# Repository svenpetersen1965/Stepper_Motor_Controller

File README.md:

# Stepper Motor Controller
The purpose of this project is top provide an Arduino (Pro Micro) based stepper motor controller with two output channels, rotary encoder, LCD display and an RS-232 interface (beside the serial via USB interface of the Pro Micro) with a 3D printed case and a software framework (Arduino Sketch) suitable for many purposes.

The 3D printed case provides different versions of the top and bottom shells. 

In case you are not experienced with cable making, you might want to read the <a href="http://tech.guitarsite.de/cable_making.html">essay about this topic on my website</a>.

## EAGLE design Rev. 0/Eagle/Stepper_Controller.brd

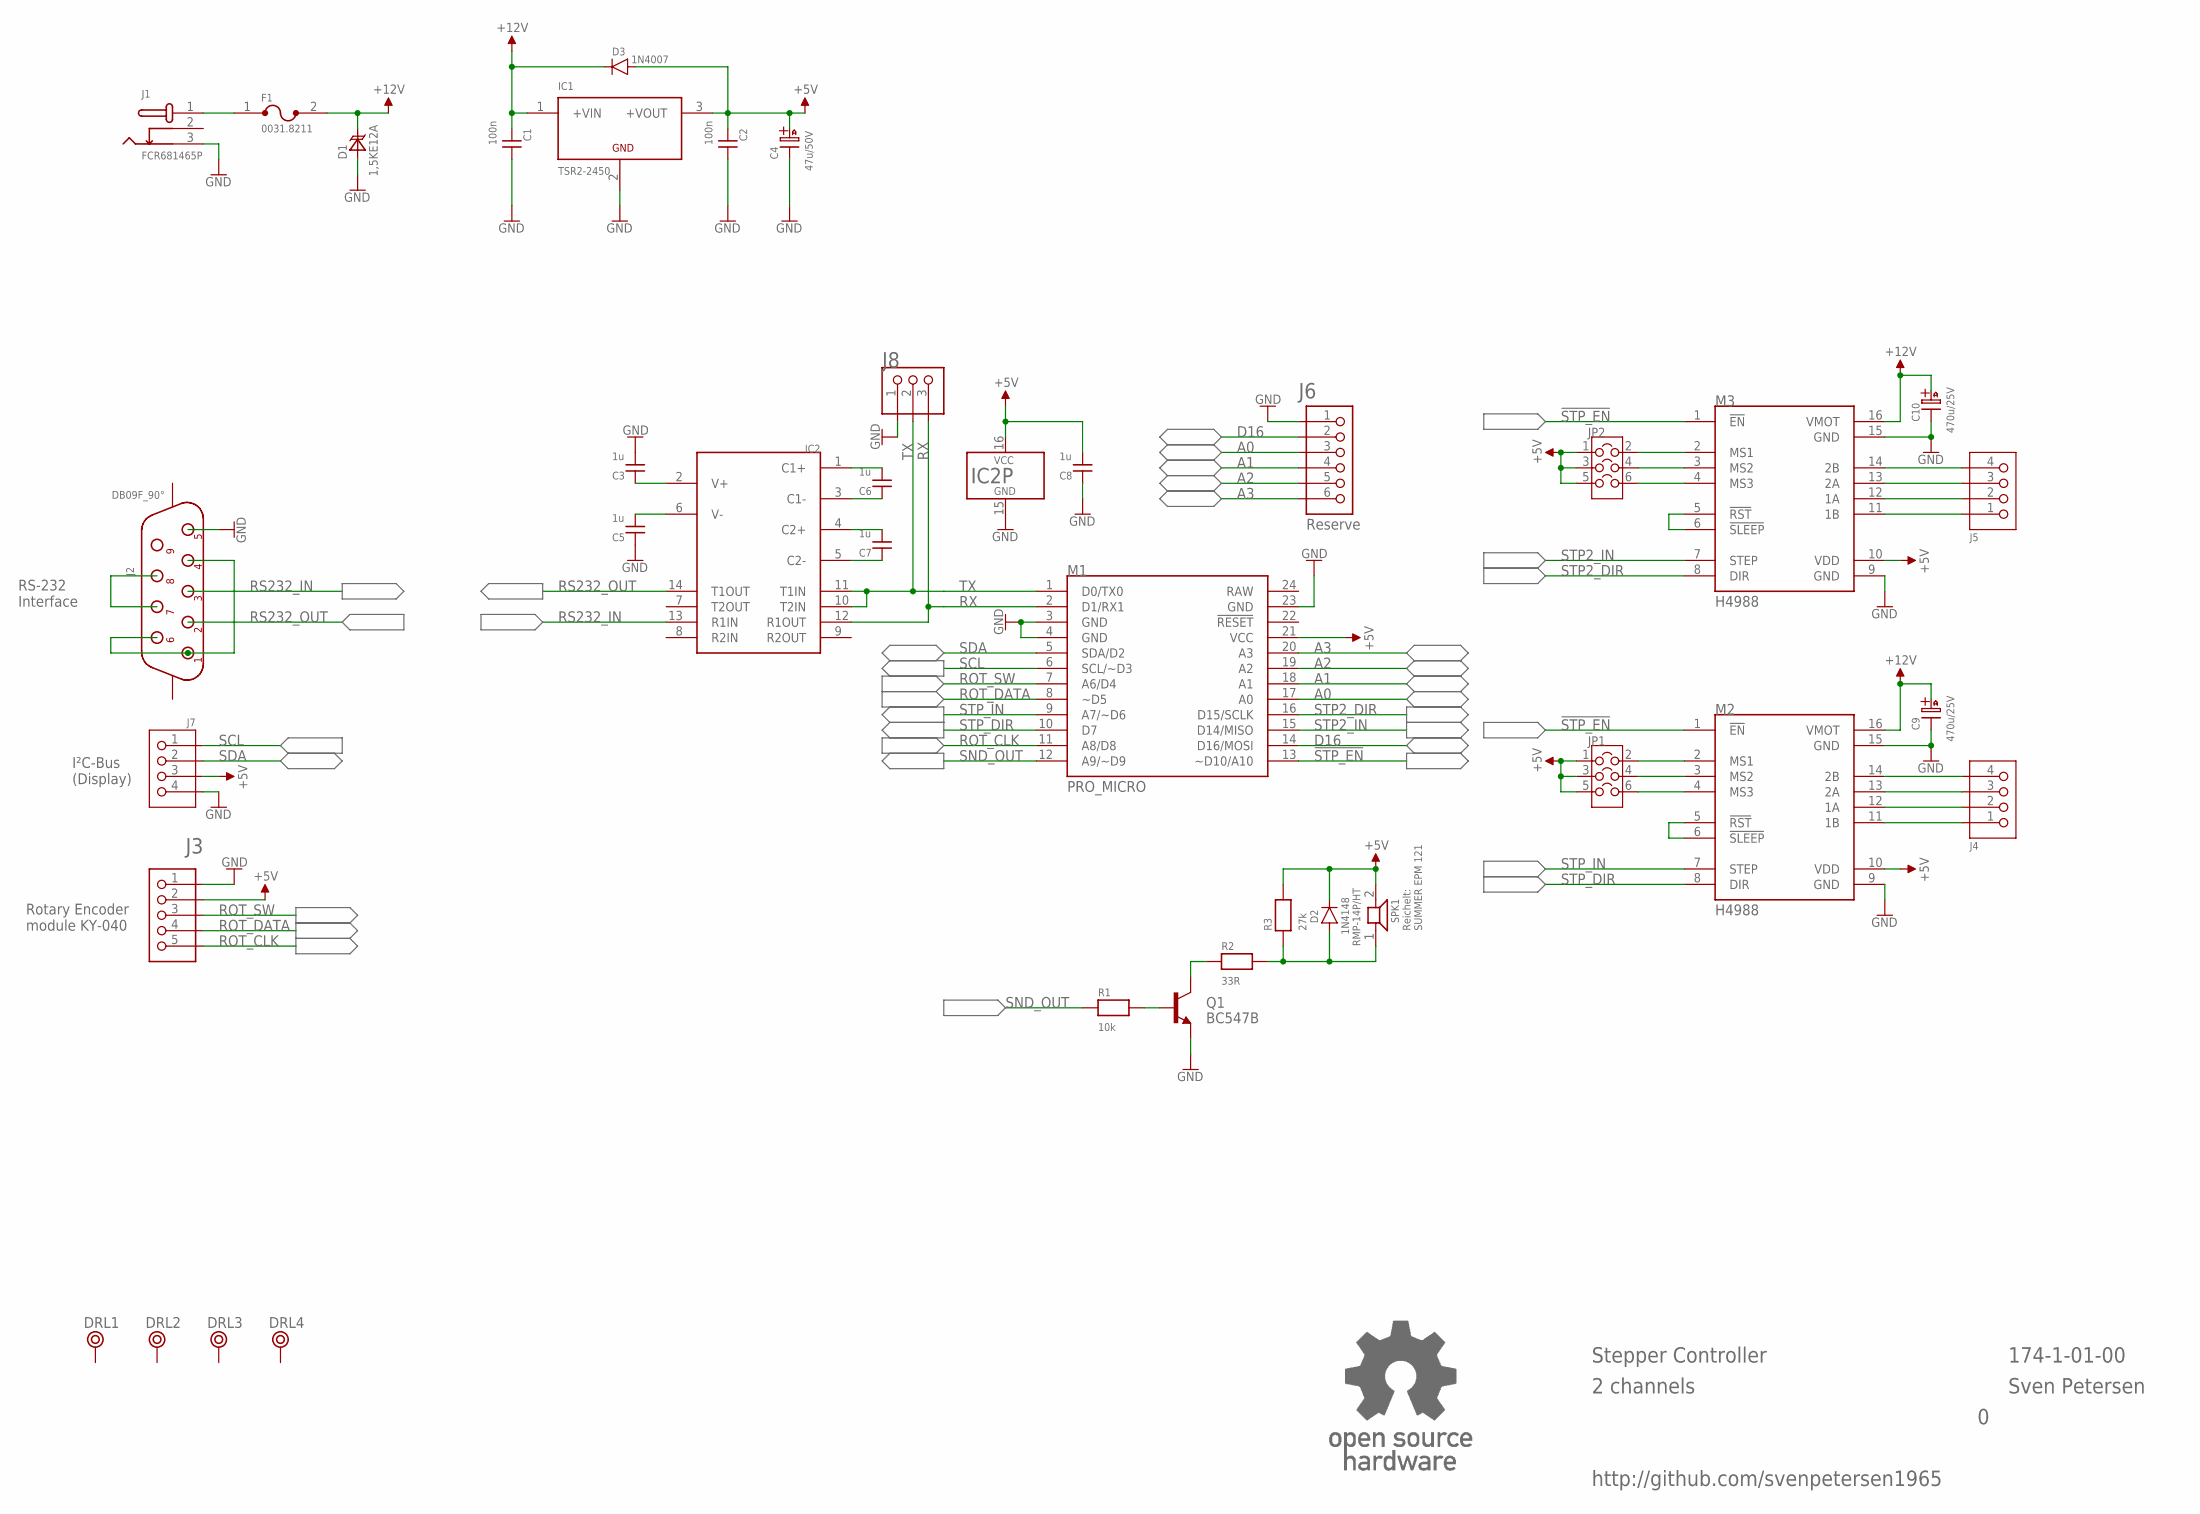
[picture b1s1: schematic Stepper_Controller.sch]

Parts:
C1, C2: 100n; C-2,5
C3, C5, C6, C7, C8: 1u; C-5
C4: 47u/50V; C07/2,5
C9, C10: 470u/25V; C08/3,5
D1: 1,5KE12A; DO-201
D2: 1N4148; DO-35
D3: 1N4007; DO-41
DRL1, DRL2, DRL3, DRL4: BOHR3,5
F1: 0031.8211
IC1: TSR2-2450; TSR2
IC2: MAX-232; DIL-16
J1: FCR681465P
J2: DB09F_90°; DS09F-H
J3: 6410-5P
J4, J5, J7: 6410-4P
J6: PINHD-1X6; 1X06
J8: PINHD-1X3; 1X03
JP1, JP2: COMBI-3X2P; COMBI-3X2
M1: PRO_MICRO
M2, M3: H4988
Q1: BC547B; TO92
R1: 10k; R-10
R2: 33R; R-10
R3: 27k; R-10
SPK1: RMP-14P/HT
U$2: OPEN_SOURCE_HW; OPENHW

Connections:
!STP_EN: M1.13 (~D10/A10), M2.1 (!EN), M3.1 (!EN)
+5V: C2.1, C4.A (+), C8.2, D2.K, D3.A, IC1.3 (+VOUT), IC2.16 (VCC), J3.2, J7.3, JP1.1, JP1.3, JP1.5, JP2.1, JP2.3, JP2.5, M1.21 (VCC), M2.10 (VDD), M3.10 (VDD), R3.2, SPK1.2
+12V: C1.1, C9.+, C10.+, D1.K, D3.K, F1.2, IC1.1 (+VIN), M2.16 (VMOT), M3.16 (VMOT)
A0: J6.3, M1.17 (A0)
A1: J6.4, M1.18 (A1)
A2: J6.5, M1.19 (A2)
A3: J6.6, M1.20 (A3)
D16: J6.2, M1.14 (D16/MOSI)
GND: C1.2, C2.2, C3.2, C4.K (-), C5.1, C8.1, C9.-, C10.-, D1.A, IC1.2 (GND), IC2.15 (GND), J1.3, J2.5, J3.1, J6.1, J7.4, J8.1, M1.3 (GND), M1.4 (GND), M1.23 (GND), M2.9 (GND), M2.15 (GND), M3.9 (GND), M3.15 (GND), Q1.1 (E)
unnamed: F1.1, J1.1
unnamed: Q1.3 (C), R2.1
unnamed: Q1.2 (B), R1.2
unnamed: J2.1, J2.4, J2.6
unnamed: J2.7, J2.8
unnamed: C7.2, IC2.4 (C2+)
unnamed: C7.1, IC2.5 (C2-)
unnamed: C6.1, IC2.3 (C1-)
unnamed: C6.2, IC2.1 (C1+)
unnamed: D2.A, R2.2, R3.1, SPK1.1
unnamed: C3.1, IC2.2 (V+)
unnamed: C5.2, IC2.6 (V-)
unnamed: M2.5 (!RST), M2.6 (!SLEEP)
unnamed: M3.5 (!RST), M3.6 (!SLEEP)
unnamed: JP2.2, M3.2 (MS1)
unnamed: JP2.4, M3.3 (MS2)
unnamed: JP2.6, M3.4 (MS3)
unnamed: JP1.2, M2.2 (MS1)
unnamed: JP1.4, M2.3 (MS2)
unnamed: JP1.6, M2.4 (MS3)
unnamed: J4.1, M2.11 (1B)
unnamed: J4.2, M2.12 (1A)
unnamed: J4.3, M2.13 (2A)
unnamed: J4.4, M2.14 (2B)
unnamed: J5.1, M3.11 (1B)
unnamed: J5.2, M3.12 (1A)
unnamed: J5.3, M3.13 (2A)
unnamed: J5.4, M3.14 (2B)
RAW: M1.24 (RAW)
ROT_CLK: J3.5, M1.11 (A8/D8)
ROT_DATA: J3.4, M1.8 (~D5)
ROT_SW: J3.3, M1.7 (A6/D4)
RS232_IN: IC2.13 (R1IN), J2.3
RS232_OUT: IC2.14 (T1OUT), J2.2
RX: IC2.12 (R1OUT), J8.3, M1.2 (D1/RX1)
SCL: J7.1, M1.6 (SCL/~D3)
SDA: J7.2, M1.5 (SDA/D2)
SND_OUT: M1.12 (A9/~D9), R1.1
STP2_DIR: M1.16 (D15/SCLK), M3.8 (DIR)
STP2_IN: M1.15 (D14/MISO), M3.7 (STEP)
STP_DIR: M1.10 (D7), M2.8 (DIR)
STP_IN: M1.9 (A7/~D6), M2.7 (STEP)
TX: IC2.10 (T2IN), IC2.11 (T1IN), J8.2, M1.1 (D0/TX0)

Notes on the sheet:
I²C-Bus (Display)
Reichelt: SUMMER EPM 121
RS-232 Interface
Rotary Encoder module KY-040
Reserve
Stepper Controller
2 channels
174-1-01-00
Sven Petersen
http://github.com/svenpetersen1965

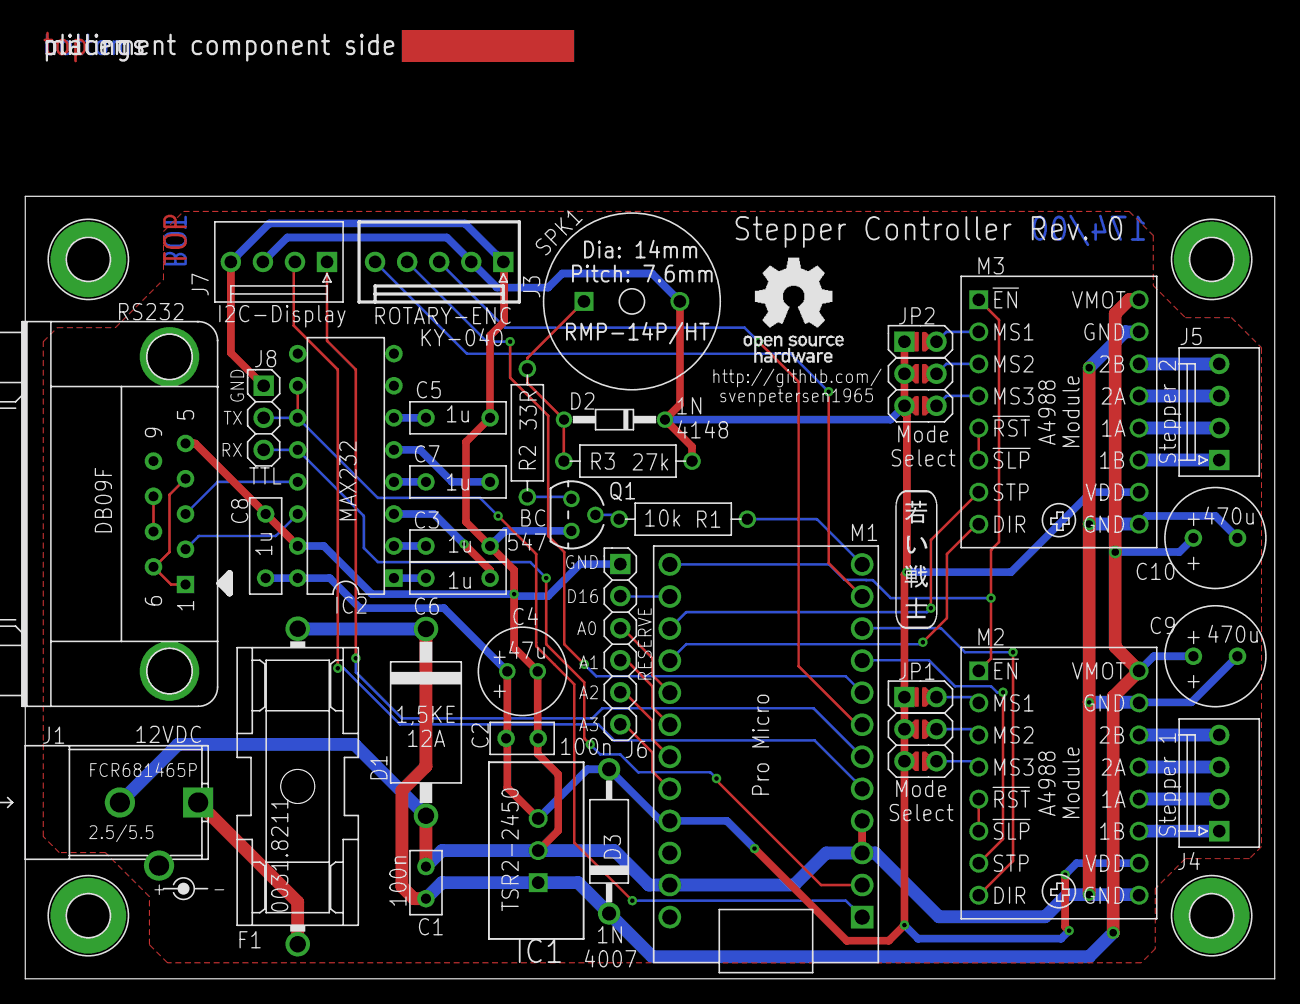
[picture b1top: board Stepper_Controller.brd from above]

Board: 2 copper layers, 99.0 x 75.6 mm, 42 parts (0 on the bottom side), 51 nets.

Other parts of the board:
U$59: PCB-TITLE/
U$71: SVEN_TAG
U$77: 2LAYER

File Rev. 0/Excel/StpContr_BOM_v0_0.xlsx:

Stepper Motor Controller Rev. 0
Bill of Material Rev. 0.0
Pos. | Qty | Value | Footprint | Ref.-No. | Comment
1 | 1 | 174-2-01-00 | 2 Layer | PCB Rev. 0 | 2 layer, Cu 35µ, HASL, 99.0mm x 62.0mm, 1.6mm FR4
2 | 2 | KF2510 (vertical, 4pin) | 6410-4P | J4, J5 | or Molex 22-27-2041 (vertical, Reichelt MOLEX 22272041 or tme.eu:MX-6410-04A) o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
3 | 1 | KF2510 (vertical, 4pin) | 6410-4P | J7 | or Molex 22-27-2041 (always vertical, Reichelt MOLEX 22272041 or tme.eu:MX-6410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
4 | 3 | KF2510 crimp housing, 4 pins |  | (J4), (J5), (J6) | or Molex 22013047 (Reichelt: MOLEX 22013047, tme.eu: MX-22-01-3047)
5 | 12 | KF2510 crimp terminals |  | (J4), (J5), (J6) | or Molex 08500114 (Reichelt: MOLEX 8500114) or Molex 08-70-0049 (tme.eu: MX-08-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
6 | 1 | KF2510 (vertical, 5pin) | 6410-5P | J3 | or Molex 22-27-2051
7 | 1 | KF2510 crimp housing, 4 pins |  | (J3) | or Molex 22013057
8 | 5 | KF2510 crimp terminals |  | (J3) | or Molex 08500114 (Reichelt: MOLEX 8500114) or Molex 08-70-0049 (tme.eu: MX-08-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
9 | 1 | MAX232CPE | DIL-16 | IC2 | Maxim or Renesas HIN232CPZ (Reichelt: MAX 232 DIP, tme.eu: HIN232CPZ)
10 | 1 | pin header, 3 pin, 2.54mm pitch | 1X03 | J8 | DNP
11 | 1 | pin header, 6 pin, 2.54mm pitch | 1X06 | J6 | DNP
12 | 1 | 0031.8211 | 318211 | F1 | Schurter fuse holder (Reichelt: PL OGN-25, tme.eu: 0031.8211)
13 | 1 | 5x20mm, 3.15AT |  | (F1) | This fuse depends on the power supply and the application
14 | 1 | 1,5KE12A | DO-201 | D1 | TVS-Diode, unidirektional, (Reichelt: 1,5KE 12A, tme.eu: 1.5KE12A-LF)
15 | 2 | 100n | C-2,5 | C1, C2 | ceramic capacitor, 2.5mm pitch
16 | 1 | 10k | R-10 | R1 | metal film resistor, 0.5W (or more), 5% or better
17 | 1 | 1N4007 | DO-41 | D3 | diode
18 | 1 | 1N4148 | DO-35 | D2 | diode
19 | 5 | 1u | C-5 | C3, C5, C6, C7, C8 | ceramic capacitor, 5mm pitch (e.g. Reichelt Z5U-5 1,0µ)
20 | 1 | 27k | R-10 | R3 | metal film resistor, 0.5W (or more), 5% or better
21 | 1 | 33R | R-10 | R2 | metal film resistor, 0.5W (or more), 5% or better
22 | 2 | 470u/25V | C08/3,5 | C9, C10 | e-cap, Æ8mm, pitch 3.5mm, 105°C, e.g. Reichelt RAD FC 470/25
23 | 1 | 47u/50V | C07/2,5 | C4 | e-cap, Æ7mm, pitch 2.5mm, 105°C, e.g. Reichelt RAD FC 47/50
24 | 1 | BC547B | TO92 | Q1 | universal NPN Transistor
25 | 2 | COMBI-3X2P | COMBI-3X2 | JP1, JP2 | see document 174-6-01-**. Reichelt MPE 087-2-006
26 | 1 | DB09F_90° | DS09F-H | J2 | D-Sub, 9pin, female, 90°, (Reichelt
27 | 1 | FCR681465P | FCR681465P | J1 | Cliff barrel connector (2.5mm/5.5mm), Reichelt: CLIFF FCR681465P, tme.eu: FCR68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
28 | 2 | A4988 | H4988 | M2, M3 | A4988 stepper driver module (AliExpress or Ebay etc.)
29 | 4 | 1x8 socket strip, 2.54mm |  | (M2), (M3) | e.g. MPE 115-1-008 (Reichelt: MPE 115-1-008, tme.eu: ZL307-1X8)
30 | 1 | PRO_MICRO | PRO_MICRO | M1 | 16MHz, 5V, Micro Controller module (Arduino compatible) from AliExpress, Ebay e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
31 | 2 | 1x12 socket strip, 2.54mm |  | (M1) | e.g. MPE 115-1-012 (Reichelt: MPE 115-1-012, tme.eu: ZL262-12SG)
32 | 1 | RMP-14P/HT | RMP-14P/HT | SPK1 | piezzo buzzer, Æ14mm, pitch 7.6mm, EKULIT (Reichelt SUMMER EPM 121): alternativ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
33 | 1 | 7805 or TSR2-2450 | TSR2 | IC1 | standard linear regulator or Traco DC/DC converter for higher supply voltages
34 | 1 | LCD Display I²C, 16x2 |  | (J7) | "standard" product from Ebay or AliExpress.
35 | 1 | dupont crimp housing, 4 pins |  |  | For the I²C Display cable
36 | 4 | Dupont crimp terminals |  |  | For the I²C Display cable
37 | 14cm | cable, AWG24, black |  |  | For the I²C Display cable, suggested color
38 | 14cm | cable, AWG24, red |  |  | For the I²C Display cable, suggested color
39 | 14cm | cable, AWG24, green |  |  | For the I²C Display cable, suggested color
40 | 14cm | cable, AWG24, grey |  |  | For the I²C Display cable, suggested color
41 | 1 | KY-040 |  |  | Rotary encoder, "standard" product from Ebay or AliExpress.
42 | 1 | dupont crimp housing, 4 pins |  |  | for the rotary encoder
43 | 4 | Dupont crimp terminals |  |  | for the rotary encoder
44 | 14cm | cable, AWG24, black |  |  | for the rotary encoder, suggested color
45 | 14cm | cable, AWG24, red |  |  | for the rotary encoder, suggested color
46 | 14cm | cable, AWG24, green |  |  | for the rotary encoder, suggested color
47 | 14cm | cable, AWG24, grey |  |  | for the rotary encoder, suggested color
48 | 14cm | cable, AWG24, blue |  |  | for the rotary encoder, suggested color

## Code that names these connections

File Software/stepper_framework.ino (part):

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#define dir2 15                    // stepper 2 direction
#define nstpena 10                 // enable both steppers (active low) 

#define rot_sw 4                   // rotary encoder switch
#define rot_data 5                 // rotary encoder data
#define rot_clk 8                  // rotary encoder clock

#define buzzer 9                   // buzzer

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  pinMode( dir2, OUTPUT );                   // dir1 is an output
  pinMode( nstpena, OUTPUT );                // nstpena is an output, that is the enable output for both stepper controlelrs

  pinMode(rot_sw, INPUT_PULLUP);             // rotary encoder: all signals input with pull-up
  pinMode(rot_data, INPUT_PULLUP);
  pinMode(rot_clk, INPUT_PULLUP);

  pinMode( buzzer, OUTPUT );                // the buzzer is an output

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
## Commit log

2021-05-23 Create LICENSE
2021-05-23 Initial Upload
